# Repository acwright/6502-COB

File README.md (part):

6502-COB
========

An **AC6502** retro-style 8-bit computer based on the **65C02** microprocessor.

> 📖 **Guide:** [AC6502 Documentation](https://acwright.github.io/6502-DOCS/) — the user's and programmer's guide for the whole family.
> See [COB's page in the family appendix](https://acwright.github.io/6502-DOCS/family/cob).

---

**Building one? Every part you need, with supplier numbers and known issues, is in [BOM.md](BOM.md).**

## Table of Contents

- [Overview](#overview)
- [Architecture](#architecture)
- [Systems](#systems)
- [Software](#software)
- [Hardware](#hardware)
  - [Backplanes](#backplanes)
  - [Cards](#cards)
  - [Helpers](#helpers)
  - [Adapters](#adapters)
- [Which revision to make](#which-revision-to-make)
- [Works with the stock BIOS](#works-with-the-stock-bios)
- [Firmware](#firmware)
  - [KEH Controller](#keh-controller)
  - [PS2 Keyboard Controller](#ps2-keyboard-controller)
  - [SCP Controller](#scp-controller)
- [CAD](#cad)
- [Production](#production)
- [Schematics](#schematics)
- [Shared lines](#shared-lines)
- [Extra pins: `EXP0`–`EXP3` and `HRDB`](#extra-pins-exp0exp3-and-hrdb)
- [Jumpers](#jumpers)
- [Off-board headers](#off-board-headers)
- [Checking the schematics](#checking-the-schematics)
- [Libraries](#libraries)
- [Bill of Materials](#bill-of-materials)
- [Purchase](#purchase)
- [License](#license)

---

## Overview

The AC6502 ecosystem is a family of open-source, 65C02-based computers sharing a common architecture, memory map, and [BIOS](https://github.com/acwright/6502-BIOS). Each computer in the family is purpose-built for a different use case but runs the same software and firmware.

The **COB** (Computer on a Backplane) is a full-featured modular desktop computer. It features a real 65C02 CPU, a backplane architecture with expandable card slots, up to 544KB RAM, composite or VGA video output, CompactFlash or SD storage, a real-time clock, and support for PS/2 keyboards, matrix keyboards, and Atari 2600-compatible joysticks.

## Architecture

All AC6502 computers share:

- **CPU**: 65C02 (or accurate emulation)
- **Memory**: 32KB RAM + 32KB ROM, with optional banked RAM expansion
- **Memory Map**: Standardized across the ecosystem — zero page, stack, I/O space ($8000–$9FFF), system ROM, and interrupt vectors at $FFFA–$FFFF
- **Bus**: 16-bit address bus, 8-bit bidirectional data bus, standard 65C02 control signals (RW, PHI2, RESET, IRQ, NMI, RDY, SYNC)
- **BIOS**: A common [BIOS](https://github.com/acwright/6502-BIOS) provides the kernel, monitor, and BASIC interpreter across all systems

## Systems

| Project | Description |
|---------|-------------|
| [6502-ACE](https://github.com/acwright/6502-ACE) | All-in-one Computer Experience — A single board computer |
| [6502-COB](https://github.com/acwright/6502-COB) | Computer On a Backplane — Modular desktop computer with expandable card slots (YOU ARE HERE) |
| [6502-DEV](https://github.com/acwright/6502-DEV) | Development Environment Vehicle — Emulation-based dev system |
| [6502-KIM](https://github.com/acwright/6502-KIM) | Keypad Input Monitor - KIM-1 inspired minimal computer |
| [6502-VCS](https://github.com/acwright/6502-VCS) | Video Computer System — Cartridge-based retro gaming console |

## Software

| Project | Description |
|---------|-------------|
| [6502-BIOS](https://github.com/acwright/6502-BIOS) | The shared BIOS (kernel, monitor, BASIC) for all AC6502 computers |
| [6502-EMULATOR](https://github.com/acwright/6502-EMULATOR) | Emulator for the whole family — desktop app, browser build, and a command line for scripted runs |
| [6502-PRG](https://github.com/acwright/6502-PRG) | Template project for writing assembly language programs |
| [6502-CRT](https://github.com/acwright/6502-CRT) | Template project for writing assembly language cartridges |
| [6502-ASM](https://github.com/acwright/6502-ASM) | Assembly language example programs and demos |
| [6502-BAS](https://github.com/acwright/6502-BAS) | BASIC program listings |
| [6502-WOZMON](https://github.com/acwright/6502-WOZMON) | Wozmon as a standalone ROM |
| [6502-NOP](https://github.com/acwright/6502-NOP) | An all-NOP ROM, for probing a board during bring-up |
| [6502-DOCS](https://github.com/acwright/6502-DOCS) | The documentation site — the guide, the printable reference cards, branding and label artwork |
| [cffs](https://github.com/acwright/cffs) | Builds CompactFlash disk images for the BIOS filesystem |
| [bastok](https://github.com/acwright/bastok) | Tokenizes BASIC listings into `.prg` images, and back |
| [bin2woz](https://github.com/acwright/bin2woz) | Converts a binary into a Wozmon serial upload |

## Hardware

This repository contains KiCad 7.0+ PCB designs for the backplanes, cards, and helpers that make up the COB system.

### Backplanes

**`Hardware/Backplane/`** — Passive backplane providing 5 card slots with full bus interconnect across all slots.

**`Hardware/Backplane Pro/`** — Enhanced backplane with integrated clock generation, reset circuitry, and power distribution plus 5 card slots. Rev 1.1 moves to entirely through-hole components and adds an onboard power switch and DC barrel jack input. Today's Rev 1.1 also removes the `RESB` pull-up, which the boards made as Rev 1.1, on sale now, still have (see the build notes in BOM.md). Use a centre-positive 5 V supply: nothing on the board protects it from a reversed one. Every revision's oscillator can is 1 MHz, and serial is tested at 1 MHz. A faster can is at the builder's risk, because the serial cards haven't been tested with one.

**`Hardware/Backplane Helper/`** — Adds additional card slots to expand the total backplane configuration up to 12 slots.

### Cards

**`Hardware/Clock Card/`** — The Backplane Pro's clock, reset and power on a card, so a COB can be built on the passive Backplane: a 1 MHz DIP-14 can oscillator to `PHI2` through a clock-enable header (so the Clock Helper's single-step and halt still work), the 555 power-on and push-button reset pulling `RESB` low through an NPN, and a 5 V barrel jack straight to `VCC`, for a centre-positive supply only (a Rev 1.0 takes a wire link in place of D2; see the build notes in BOM.md). Serial is tested at 1 MHz, so a faster oscillator can is at the builder's risk, as on the Backplane Pro.

**`Hardware/CPU Card/`** — Hosts the 65C02 CPU in a card form factor for backplane-based COB systems. Its `EXP` header, J3, can jumper `EXP0` to VPB and `EXP1` to MLB. Leave those two positions open in a build that takes cartridges, because a cartridge grounds `EXP0` and `EXP1` (see [Extra pins](#extra-pins-exp0exp3-and-hrdb)).

**`Hardware/CPU Card Pro/`** — Hosts a 65816 16-bit CPU (backward-compatible with 65C02). *(Untested)* Its title block credits bahamutkotd, who contributed. Its `EXP` header, J3, can jumper `EXP0` to VPB and `EXP1` to MLB; as on the CPU Card, leave those positions open in a build that takes cartridges. J2, `BANK ADDR`, carries the 65816's bank byte (address bits A16–A23), which U4 latches while `PHI2` is low and holds through the rest of the cycle. It is how a 65816 on this card reaches past 64 KB, for a breadboard or a card of your own. Nothing in the family uses it yet, and it is unproven until the card is built. The RAM Card Rev 1.0's J4 has the same pinout; see its build notes before joining the two.

**`Hardware/Memory Card/`** — Provides 32KB SRAM and 32KB EEPROM with address decoding logic for COB systems using the CPU Card. J2 (or the solder jumpers JP1 and JP2) joins the bus's `EXP1` and `EXP0` to the ROM's `HRDB`: fit both in a COB that takes cartridges. See [Extra pins](#extra-pins-exp0exp3-and-hrdb).

**`Hardware/RAM Card/`** — 512KB banked RAM expansion organized as two 256KB banks with 256 × 1KB windows each. Rev 1.1 has the ACE Board's circuit, with a bank latch for each window; Rev 1.0 has one latch for both. Rev 1.0's J4, `BANK ADDR`, carries the bank latch's outputs: an untested experiment that nothing in the family uses, which the build notes in [BOM.md](BOM.md#ram-card) explain.

**`Hardware/RTC Card/`** — Real-time clock via Dallas DS1511Y with battery backup and 256 bytes of battery-backed SRAM. Any revision also takes the [RTC Adapter](#adapters), a cheaper DS1501 on a plug, and Rev 1.1 takes a bare DS1501, the same chip without the module's crystal and cell, with the crystal on the card; [BOM.md's build notes](BOM.md#build-notes) say what each needs.

**`Hardware/GPIO Card/`** — General-purpose I/O via 65C22 VIA supporting keyboards, joysticks, timers, and custom devices.

**`Hardware/Serial Card/`** — RS-232 serial communication via R6551AP ACIA and MAX232 level shifter.
Female DB-9 wired as **DCE**, so a straight-through cable reaches a PC. `DCD` and `DSR` are tied to
ground; `DTR` is not connected. The `CTS EN` jumper (J4) picks whether the ACIA's `CTS` comes from
ground or from the cable — **ground is the default**, which leaves the transmitter always free to
send. Serial is tested at 1 MHz, the speed of the oscillator can on the Backplane Pro and the Clock
Card. A faster can is at the builder's risk.

**`Hardware/Serial Card Pro/`** — Enhanced serial card with full modem control signals (DTR, DCD, DSR).
Male DB-9 wired as **DTE**, like a PC, so reaching a laptop needs a **null-modem** cable — unlike the
plain Serial Card. `CTS`, `DSR` and `DTR` always reach the cable; the `DCD EN` jumper picks ground or
the cable for `DCD` — **ground is the default**. Serial is tested at 1 MHz, the speed of the
oscillator can on the Backplane Pro and the Clock Card. A faster can is at the builder's risk.

**The handshake lines are not decoration.** On a real R6551, measured on a KIM in 2026: `CTS` high
stops the transmitter dead, and `DCD` high stops the receiver and the arriving byte is lost. A card
jumpered to take either from the cable, plugged into something that does not assert them, looks like
a dead board — no banner, no echo — until the line comes back. Ground is the default for exactly
that reason.

**`Hardware/VGA Card/`** — VGA 640×480 video output via Raspberry Pi Pico running [Pico9918](https://github.com/visrealm/pico9918) with TMS9918A-compatible graphics modes.

**`Hardware/Video Card/`** — Composite video output via TMS9918A Video Display Processor with 16KB video RAM.

**`Hardware/Sound Card/`** — 3-voice SID audio output via ARMSID module with RCA line-level output.

**`Hardware/Storage Card/`** — CompactFlash storage interface supporting up to 128GB via IDE-compatible protocol.

**`Hardware/Storage Card Pro/`** — SD card storage that the stock BIOS takes for the Storage Card's CompactFlash card, with no BIOS change, and a 16 MB built-in drive that answers when no card is in. A Raspberry Pi Pico 2 module does the work, running the [SCP Controller](#scp-controller). *(Untested: Rev 1.1 is drawn and routed, not yet made.)*

**`Hardware/LCD Card/`** — 16×2 character LCD display via 65C22 VIA in 4-bit or 8-bit mode.

**`Hardware/Blinkenlights Card/`** — Visual bus monitoring with LEDs showing address bus (16), data bus (8), and control signals (8) in real time.

**`Hardware/Prototype Card/`** — Blank prototyping area with integrated breadboard and full bus access headers.

### Helpers

**`Hardware/Keyboard Encoder Helper/`** — ATmega1284-based dual keyboard encoder supporting PS/2 keyboard and 8×8 matrix keyboard simultaneously via 65C22 VIA.

**`Hardware/PS2 Helper/`** — ATmega328p-based PS/2 keyboard bridge that drives an MT8808 analog crosspoint switch to emulate a matrix keyboard. Its output is a raw 8×8 matrix and feeds the matrix inputs of a Keyboard Encoder Helper, which is what talks to the 65C22 VIA — not the VIA directly.

**`Hardware/Keyboard Helper/`** — 64-key matrix keyboard with Atari 2600-compatible joystick support.

**`Hardware/GPIO Helper/`** — 8 buttons and 8 LEDs for testing and debugging GPIO Card connections.

**`Hardware/GPIO Breadboard Helper/`** — Breadboard interface adapter for the GPIO Card.

**`Hardware/Joystick Helper/`** — Atari 2600-style dual joystick connector and interface board.

**`Hardware/Clock Helper/`** — Manual clock control providing single-step, free-run, and halt modes for debugging real CPU systems.

**`Hardware/DB25 Helper/`** — GPIO to DB25 connector adapter for external device interfacing.

**`Hardware/Breadboard Helper/`** — Exposes the full AC6502 bus to a breadboard for prototyping and experimentation.

**`Hardware/Mega Helper/`** — Arduino Mega 2560 interface adapter for the AC6502 bus. Arduino pins D6 and D5 are wired to `EXP1` and `EXP0`: with a cartridge on the bus, firmware must leave them as inputs, because the cartridge grounds them (see [Extra pins](#extra-pins-exp0exp3-and-hrdb)).

**LCD Board** — moved to [6502-DEV](https://github.com/acwright/6502-DEV) as the DEV LCD Board on 2026-11-14: it is a DEV board.

**`Hardware/VERA Helper/`** — VERA FPGA video module adapter for the AC6502 bus.

### Adapters

**`Hardware/RTC Adapter/`** — A DS1501 real-time clock and its 32.768 kHz crystal on a DIP-28 plug, in place of the DS1511Y. The DS1511Y is a DS1501 with its crystal and a lithium cell in one module, and the family's most expensive chip: $41.36 at Digi-Key, against $23.19 for the adapter's DS1501YZN+ (2026-11-19). The adapter plugs into the DS1511Y's socket on any RTC Card or [ACE Board](https://github.com/acwright/6502-ACE#the-rtc), Rev 1.0 included, and fits inside the module's outline. The BIOS runs it as it runs the DS1511Y: the registers, the 256 bytes of NVRAM and the pinout are the same. The plug's pins 2, 3, 21 and 25 connect to nothing, so the adapter's crystal is never in parallel with a 1.1 board's own. *(Untested)*

Which RTC each board takes:

| Board | Rev | DS1511Y | RTC Adapter | DS1501 (DIP) |
|---|---|---|---|---|
| RTC Card | 1.0 | Yes, the part it was made and tested with | Yes, untested | No: it has no crystal |
| RTC Card | 1.1 | Yes | Yes, untested | Yes, untested |
| ACE Board | 1.0 | Yes, the part it was made and tested with | Yes, untested | No: it has no crystal |
| ACE Board | 1.1 | Yes | Yes, untested | Yes, untested |

With the RTC Adapter or a DS1501:
- **Keep the CR2032 fitted.** It is the DS1501's only backup, so taking it out loses the time and the NVRAM. A DS1511Y has its own cell as well.
- **Use BIOS 1.8 or 2.2.0 or later.** A new DS1501 may start with its Crystal Select bit set, and then it runs slow on the 6 pF crystal; the BIOS clears the bit at every boot from those releases on ([6502-BIOS #4](https://github.com/acwright/6502-BIOS/issues/4)).
- **The DS1501YN+, the DIP chip, is not for new designs** (NRND). The adapter's DS1501YZN+, in SOIC, is active.

[BOM.md's build notes](BOM.md#build-notes) say how to build the adapter.

<!-- Which revision to make: generated by Tools/revision-audit/register.py from Tools/data/orders.json. Edit that file, not this section. -->
## Which revision to make

**Make the newest revision of a board, and check its label first.** The table below gives each board's newest revision. A newer revision fixes what was found on the older ones. Every revision, old and new, is in [REVISIONS.md](REVISIONS.md), with what changed in each.

Each revision carries one of three labels:

- **Tested:** This revision was built and tested.
- **Proven design:** Not built at this revision, but its circuit is proven. Either it is a tested revision's circuit, or each change copies a circuit built and tested on another board or on the bench, or is a textbook circuit that leaves everything the tested revision does as it was. Any other change is silkscreen text, part values, mounting holes, outline clean-up, parts moved a fraction of a millimetre onto their grid, capacitor pitch, socket outlines, a footprint swap with the same holes, a solder jumper's default, the solder mask or paste at a card edge, or tracks rerouted or pours refilled with DRC and the netlist check passing. A builder can treat it as tested.
- **Untested:** The circuit, the power path or the layout changed in a way that only a built board proves, or the board has never been built at all.

[BOM.md](BOM.md) has the parts for every revision, and its known issues.

| Board | Newest revision | Label | Why |
|---|---|---|---|
| Backplane | 1.1 | **Proven design** | JLCPCB's marker removed and the logo moved; silkscreen only. |
| Backplane Helper | 1.1 | **Proven design** | JLCPCB's marker removed and the logo moved; silkscreen only. |
| Backplane Pro | 1.1 | **Proven design** | The tested boards made as Rev 1.1, with R5, a second pull-up on `RESB` beside the CPU Card's, left off. Nothing else changed. |
| Blinkenlights Card | 1.1 | **Untested** | Decoupling capacitors added, the RESB, IRQB and NMIB LEDs driven through inverters, every inverter a 74HC3G04, tracks rerouted, and the bare card edge. |
| Breadboard Helper | 1.1 | **Proven design** | J1 takes the box header's footprint, with the same holes, and the outline grows to hold it. |
| CPU Card | 1.1 | **Proven design** | 10k pull-ups, some tracks rerouted, silkscreen, the bare card edge. |
| CPU Card Pro | 1.1 | **Untested** | Never made. |
| Clock Card | 1.1 | **Proven design** | The bare card edge only. |
| Clock Helper | 1.1 | **Proven design** | Mounting holes moved to the standard, silkscreen. |
| DB25 Helper | 1.1 | **Proven design** | Mounting holes moved to the standard, silkscreen. |
| GPIO Breadboard Helper | 1.1 | **Proven design** | Outline clean-up. |
| GPIO Card | 1.1 | **Proven design** | The bare card edge only. |
| GPIO Helper | 1.1 | **Proven design** | Mounting holes moved to the standard, silkscreen. |
| Joystick Helper | 1.1 | **Proven design** | Mounting holes moved to the standard, silkscreen. |
| Keyboard Encoder Helper | 1.1 | **Proven design** | Mounting holes, silkscreen, and 10k pull-ups on the PS/2 lines, a textbook circuit not yet tried on these lines. |
| Keyboard Helper | 1.1 | **Proven design** | JLCPCB's marker removed and the logo moved; silkscreen only. |
| LCD Card | 1.1 | **Proven design** | The bare card edge only. |
| Mega Helper | 1.1 | **Proven design** | JLCPCB's marker removed, J1's reference resized and the logo moved; silkscreen only. |
| Memory Card | 1.1 | **Proven design** | The bare card edge only. |
| PS2 Helper | 1.1 | **Proven design** | Resistors moved and tracks rerouted, mounting holes, silkscreen, and 10k pull-ups on the PS/2 lines, a textbook circuit not yet tried on these lines. |
| Prototype Card | 1.1 | **Proven design** | The bare card edge only. |
| RAM Card | 1.1 | **Proven design** | The ACE's banked-RAM circuit, tested as the ACE RAM Patch 1.1: a bank latch for each window and a diode chip select (BAT54s in the BAT85s' place). The window decode is Rev 1.0's, and the `LATCH EN` and `BANK ADDR` headers are gone. Tracks rerouted, with the decode check passing in every window. |
| RTC Adapter | 1.1 | **Untested** | A new board: a DS1501 in SOIC and its crystal on a DIP-28 plug, for the DS1511Y's socket on any RTC Card or ACE Board. Not yet made. |
| RTC Card | 1.1 | **Proven design** | The bare card edge, and JP2 and JP3 removed, wired as Rev 1.0 ships them. The DS1501 option at U1, with its crystal `Y1`, is untested. |
| Serial Card | 1.1 | **Proven design** | Silkscreen text and the bare card edge. |
| Serial Card Pro | 1.1 | **Proven design** | The DB-9 moved to KiCad's standard footprint (the same connector), tracks rerouted, silkscreen, the bare card edge. |
| Sound Card | 1.1 | **Proven design** | Silkscreen text, the bare card edge, and a second RCA jack on the same signal, as on the ACE. |
| Storage Card | 1.1 | **Proven design** | The bare card edge only. |
| Storage Card Pro | 1.1 | **Untested** | Redesigned: an SD card the stock BIOS takes for CompactFlash, with a built-in drive. Not yet made. |
| VERA Helper | 1.1 | **Proven design** | Mounting holes, capacitor pitch, JP2 ships open, JP1 and JP3 removed and wired as Rev 1.0 ships them. |
| VGA Card | 1.1 | **Proven design** | `A1` wired to the pico9918's `MODE1`, as on the tested ACE; JP1 open, so `/INT` passes only through D1, as the ACE's video card runs; `PHI2` wired to U3 as Rev 1.0 ships, with JP2 and JP3 gone. The pico9918 is turned around with its tracks rerouted, the notch and holes for its VGA adapter moved, and the card edge bare. |
| Video Card | 1.1 | **Proven design** | JP7, a solder jumper, ships bridged (fine with a real TMS9918A's open-drain `/INT`), JP1–JP6 removed and wired as Rev 1.0 ships them, sockets, silkscreen, the bare card edge. |
<!-- End of which revision to make -->

<!-- Stock BIOS: generated by Tools/bios/gen.py from Tools/data/bios.json. Edit that file, not this section. -->
## Works with the stock BIOS

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
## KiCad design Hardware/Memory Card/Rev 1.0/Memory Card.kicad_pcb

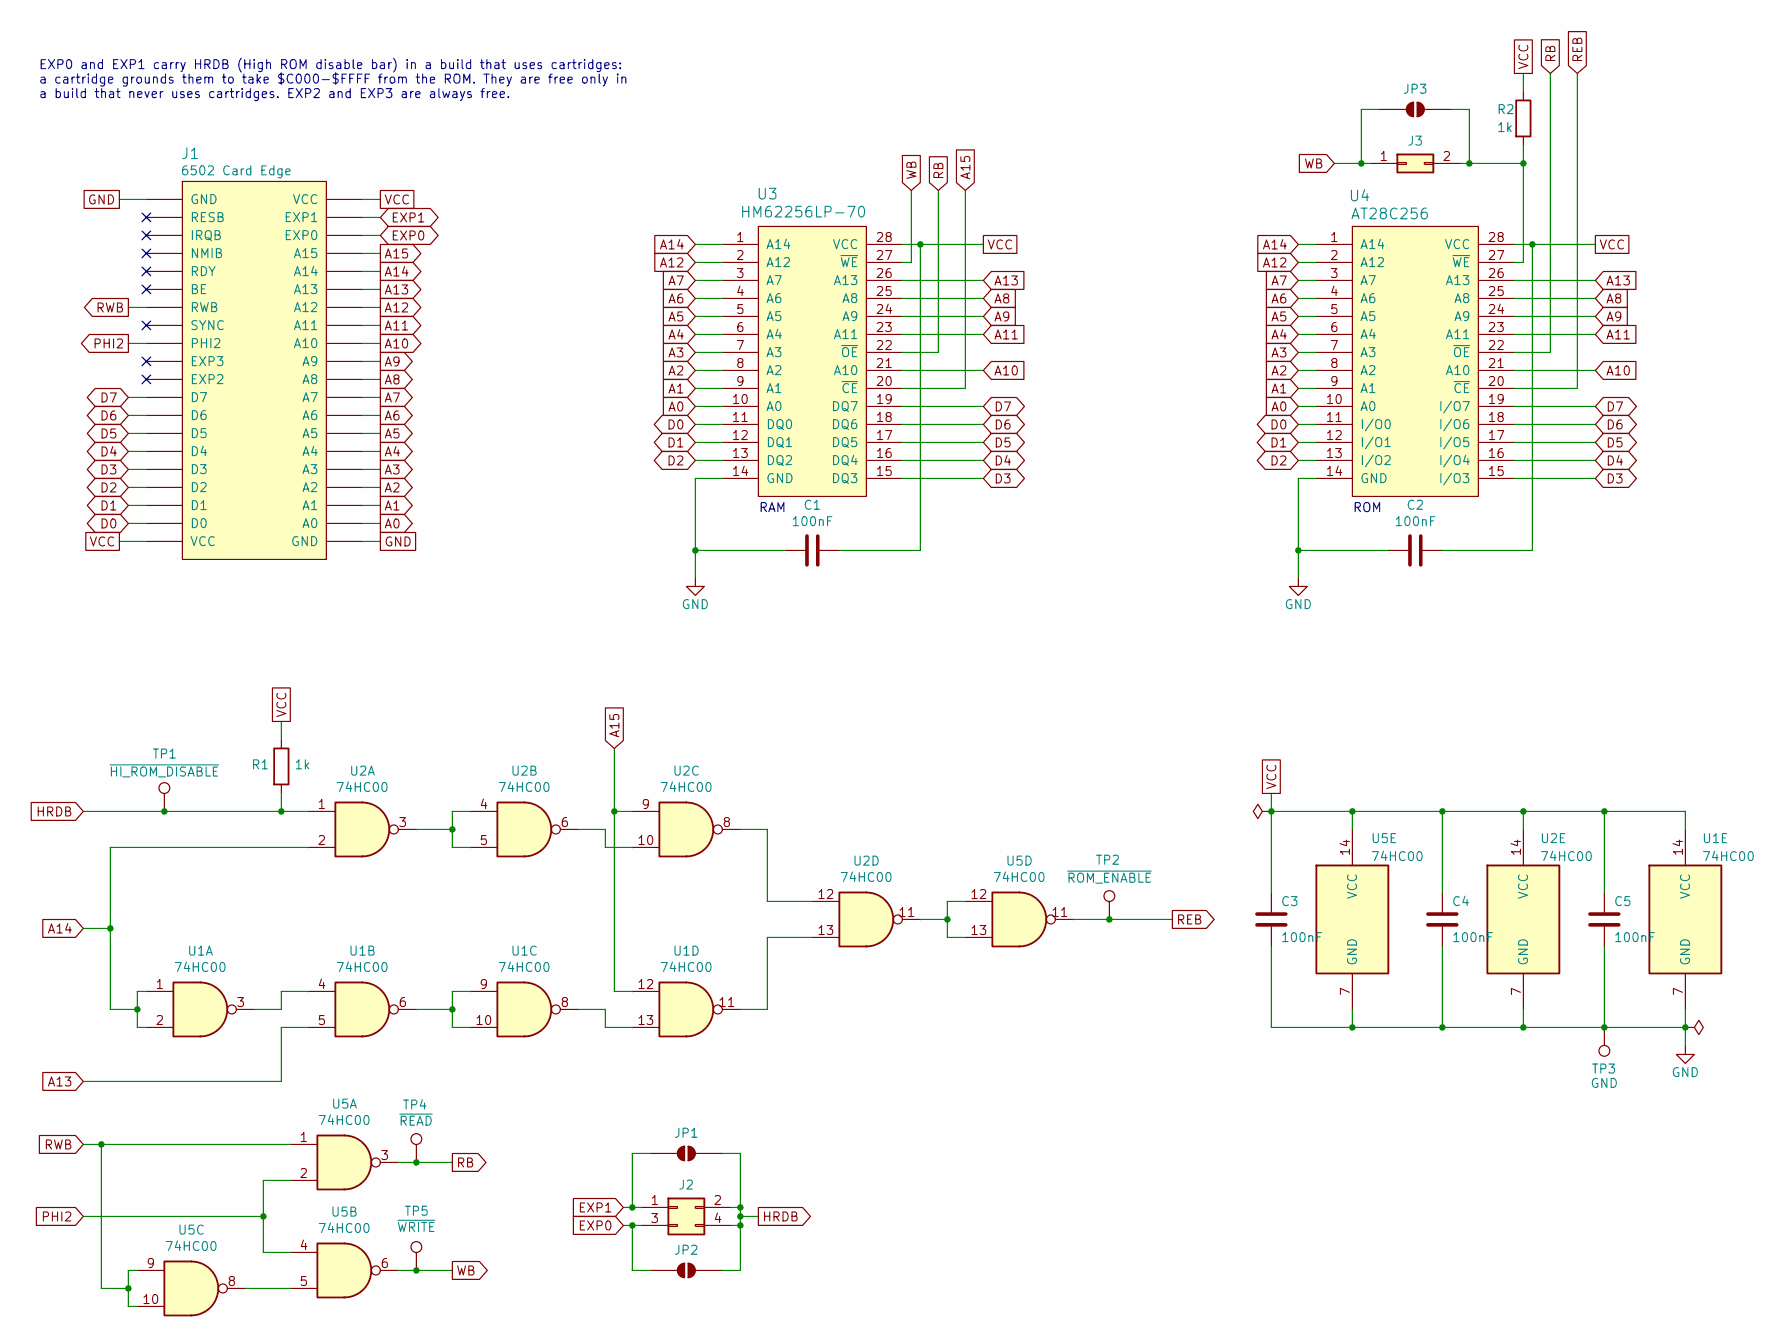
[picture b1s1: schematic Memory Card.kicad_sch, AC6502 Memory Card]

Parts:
C1, C2, C3, C4, C5: 100nF; C_0805_2012Metric; LCSC C49678
J1: 6502 Card Edge
J2: Conn_02x02_Odd_Even; PinHeader_2x02_P2.54mm_Vertical; Digikey S2011EC-40-ND
J3: Conn_02x01; PinHeader_1x02_P2.54mm_Vertical; Digikey S1011EC-40-ND
JP1, JP2, JP3: SolderJumper_2_Open; SolderJumper-2_P1.3mm_Open_RoundedPad1.0x1.5mm
R1, R2: 1k; R_0805_2012Metric; LCSC C17513
TP1: ~{HI_ROM_DISABLE}; TestPoint_Pad_1.0x1.0mm
TP2: ~{ROM_ENABLE}; TestPoint_Pad_1.0x1.0mm
TP3: GND; TestPoint_Pad_1.0x1.0mm
TP4: ~{READ}; TestPoint_Pad_1.0x1.0mm
TP5: ~{WRITE}; TestPoint_Pad_1.0x1.0mm
U1, U2, U5: 74HC00; SOIC-14_3.9x8.7mm_P1.27mm; LCSC C5586
U3: HM62256LP-70; DIP-28_W15.24mm_Socket_LongPads
U4: AT28C256; DIP-28_W15.24mm_Socket_LongPads; Digikey AT28C256-15PU-ND

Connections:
A0: J1.A0, U3.10 (A0), U4.10 (A0)
A1: J1.A1, U3.9 (A1), U4.9 (A1)
A2: J1.A2, U3.8 (A2), U4.8 (A2)
A3: J1.A3, U3.7 (A3), U4.7 (A3)
A4: J1.A4, U3.6 (A4), U4.6 (A4)
A5: J1.A5, U3.5 (A5), U4.5 (A5)
A6: J1.A6, U3.4 (A6), U4.4 (A6)
A7: J1.A7, U3.3 (A7), U4.3 (A7)
A8: J1.A8, U3.25 (A8), U4.25 (A8)
A9: J1.A9, U3.24 (A9), U4.24 (A9)
A10: J1.A10, U3.21 (A10), U4.21 (A10)
A11: J1.A11, U3.23 (A11), U4.23 (A11)
A12: J1.A12, U3.2 (A12), U4.2 (A12)
A13: J1.A13, U1.5, U3.26 (A13), U4.26 (A13)
A14: J1.A14, U1.1, U1.2, U2.2, U3.1 (A14), U4.1 (A14)
A15: J1.A15, U1.12, U2.9, U3.20 (~CE)
D0: J1.D0, U3.11 (DQ0), U4.11 (I/O0)
D1: J1.D1, U3.12 (DQ1), U4.12 (I/O1)
D2: J1.D2, U3.13 (DQ2), U4.13 (I/O2)
D3: J1.D3, U3.15 (DQ3), U4.15 (I/O3)
D4: J1.D4, U3.16 (DQ4), U4.16 (I/O4)
D5: J1.D5, U3.17 (DQ5), U4.17 (I/O5)
D6: J1.D6, U3.18 (DQ6), U4.18 (I/O6)
D7: J1.D7, U3.19 (DQ7), U4.19 (I/O7)
EXP0: J1.EXP0, J2.3, JP2.1 (A)
EXP1: J1.EXP1, J2.1, JP1.1 (A)
GND: C1.2, C2.2, C3.2, C4.2, C5.2, J1.GND, TP3.1, U1.7 (GND), U2.7 (GND), U3.14 (GND), U4.14 (GND), U5.7 (GND)
HRDB: J2.2, J2.4, JP1.2 (B), JP2.2 (B), R1.2, TP1.1, U2.1
unnamed: J3.2, JP3.2 (B), R2.2, U4.27 (~WE)
unnamed: U1.3, U1.4
unnamed: U1.6, U1.9, U1.10
unnamed: U1.11, U2.13
unnamed: U1.8, U1.13
unnamed: U2.3, U2.4, U2.5
unnamed: U2.6, U2.10
unnamed: U2.11, U5.12, U5.13
unnamed: U2.8, U2.12
unnamed: U5.5, U5.8
PHI2: J1.PHI2, U5.2, U5.4
RB: TP4.1, U3.22 (~OE), U4.22 (~OE), U5.3
REB: TP2.1, U4.20 (~CE), U5.11
RWB: J1.RWB, U5.1, U5.9, U5.10
VCC: C1.1, C2.1, C3.1, C4.1, C5.1, J1.VCC, R1.1, R2.1, U1.14 (VCC), U2.14 (VCC), U3.28 (VCC), U4.28 (VCC), U5.14 (VCC)
WB: J3.1, JP3.1 (A), TP5.1, U3.27 (~WE), U5.6

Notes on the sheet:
RAM
ROM
EXP0 and EXP1 carry HRDB (High ROM disable bar) in a build that uses cartridges: a cartridge grounds them to take $C000-$FFFF from the ROM. They are free only in a build that never uses cartridges. EXP2 and EXP3 are always free.

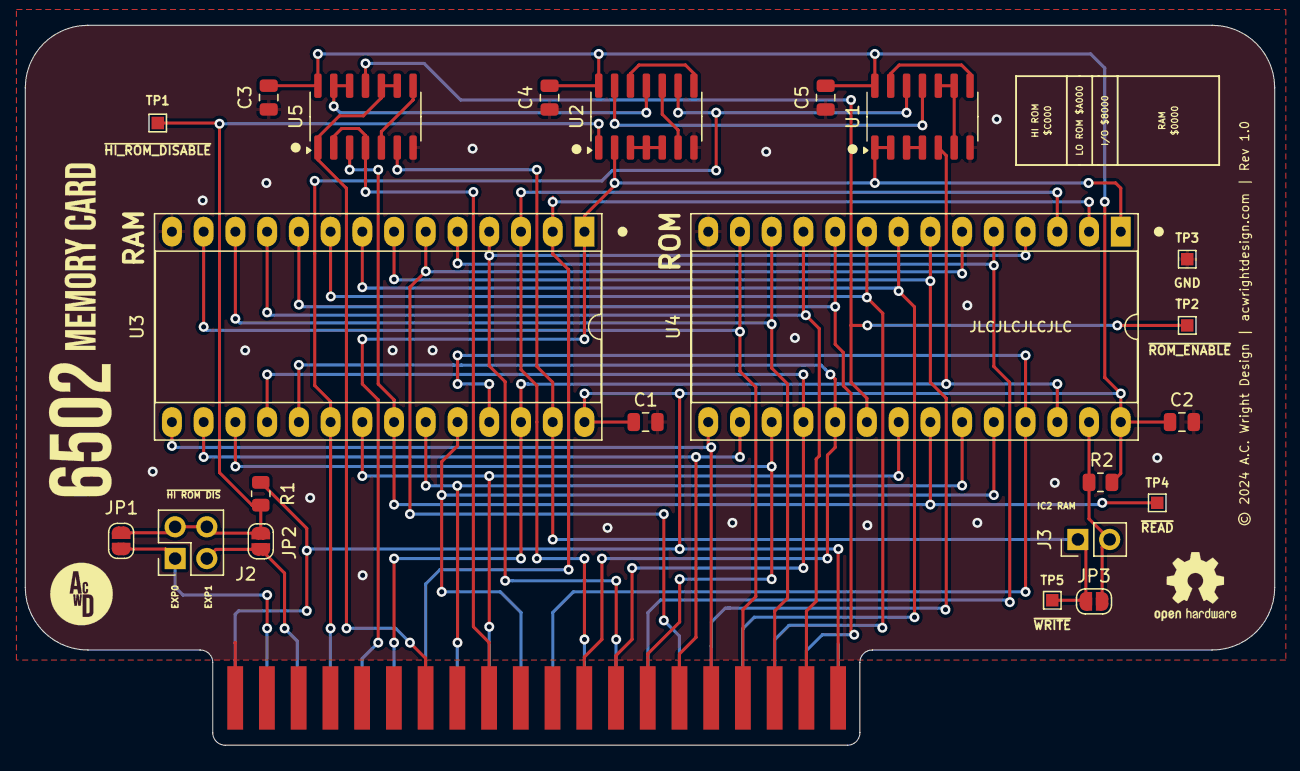
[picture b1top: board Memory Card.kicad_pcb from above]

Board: 2 copper layers, 100.0 x 57.6 mm, 23 parts (0 on the bottom side), 44 nets.

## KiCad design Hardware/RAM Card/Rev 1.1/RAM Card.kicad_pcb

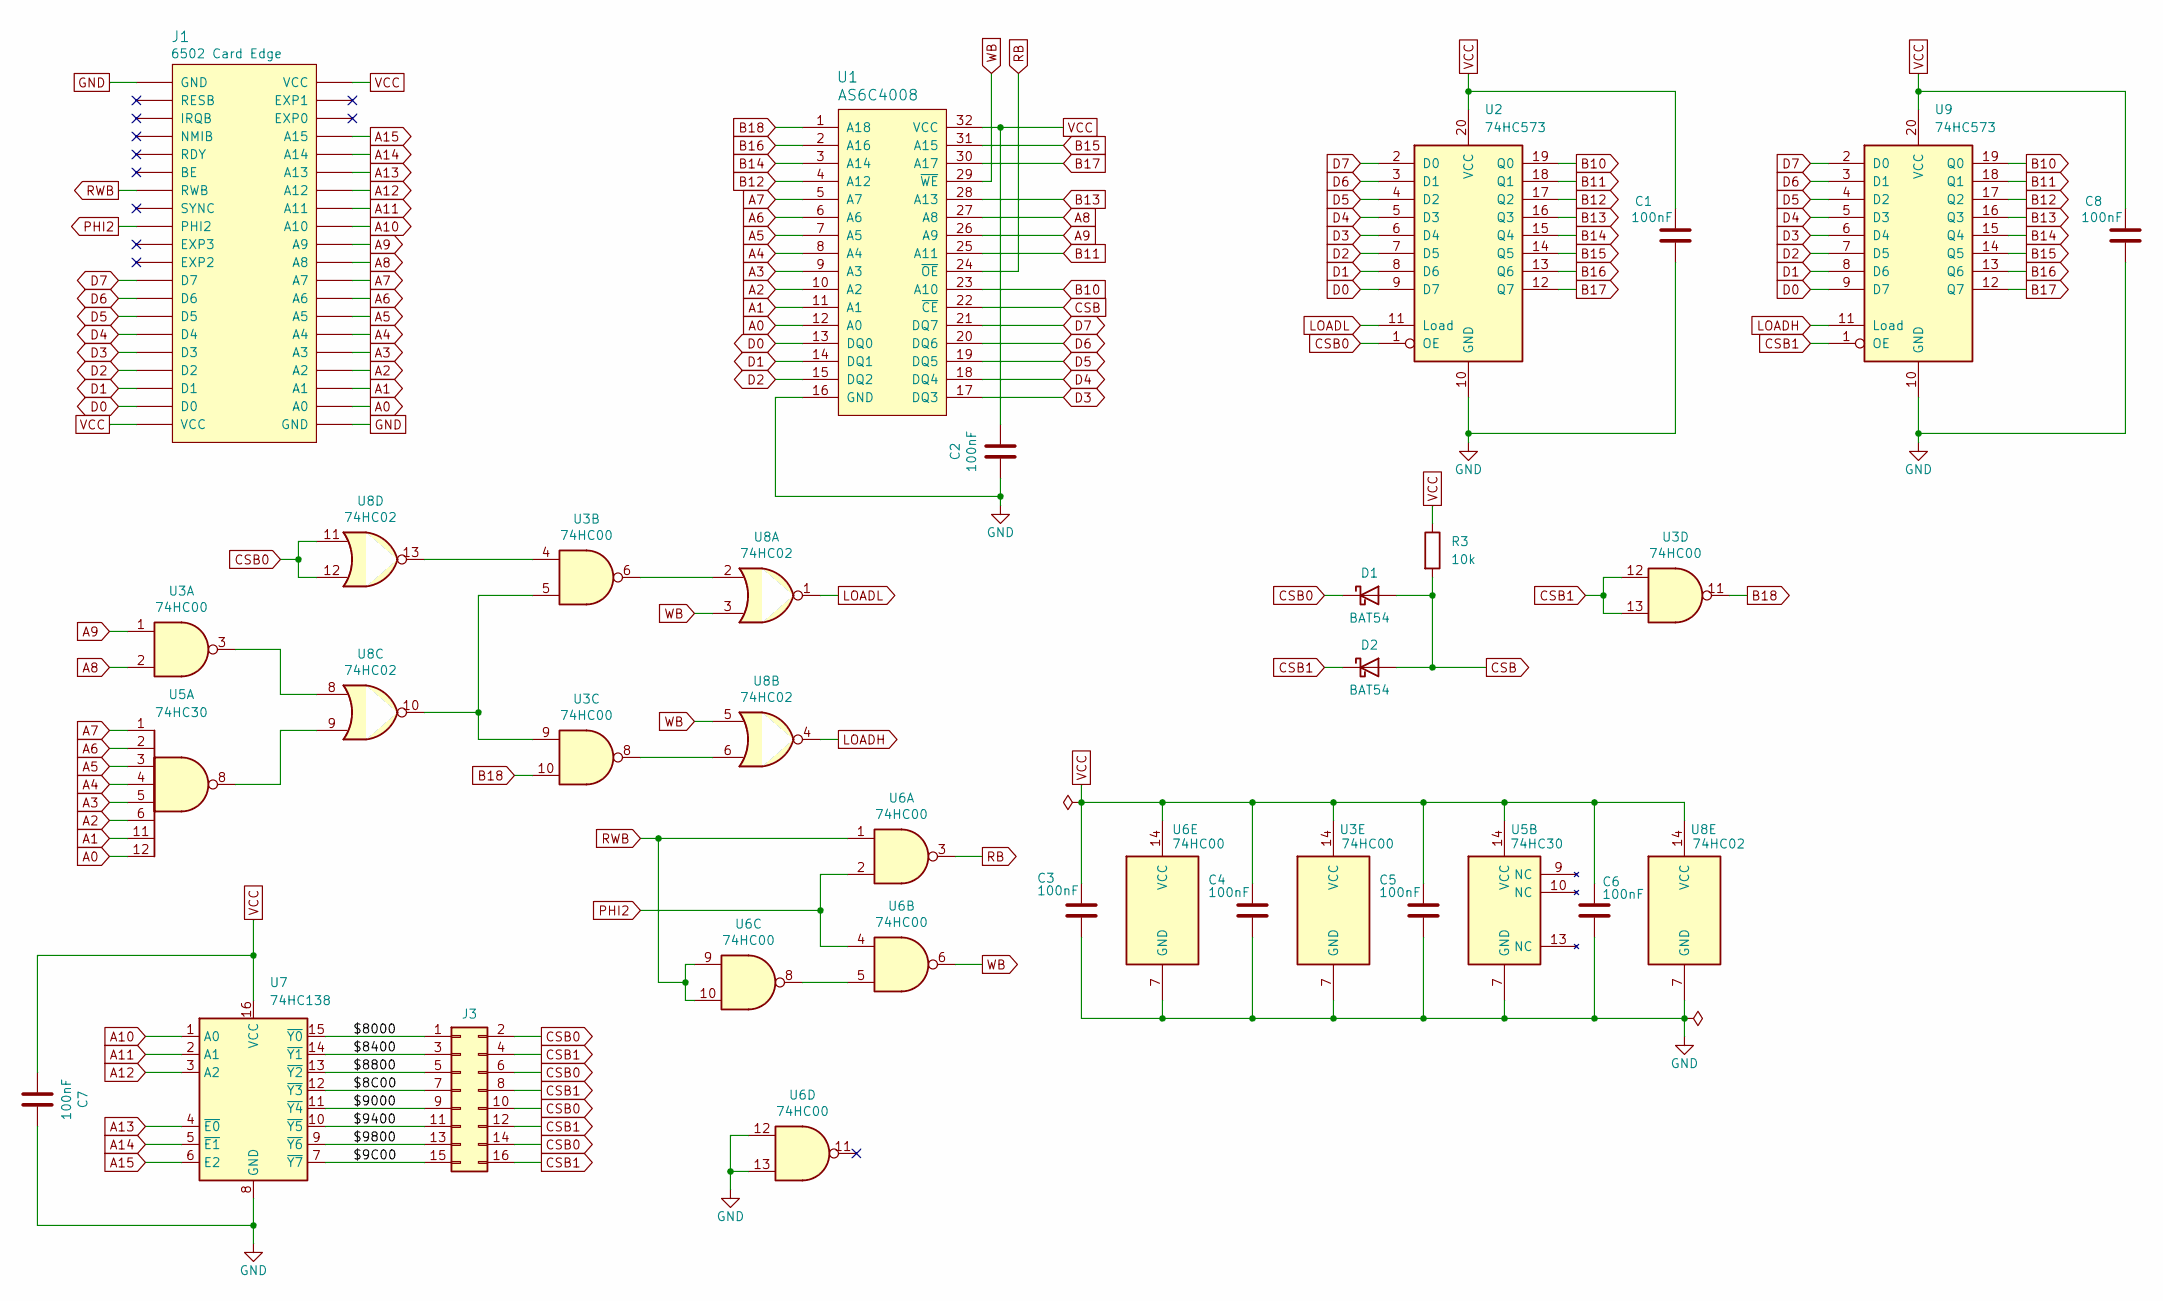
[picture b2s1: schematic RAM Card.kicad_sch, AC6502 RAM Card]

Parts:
C1, C2, C3, C4, C5, C6, C7, C8: 100nF; C_0805_2012Metric; LCSC C49678
D1, D2: BAT54; D_SOD-123; LCSC C152458
J1: 6502 Card Edge
J3: Conn_02x08_Odd_Even; PinHeader_2x08_P2.54mm_Vertical; Digikey S2011EC-40-ND
R3: 10k; R_0805_2012Metric; LCSC C17414
U1: AS6C4008; DIP-32_W15.24mm_Socket_LongPads; Digikey 1450-1027-ND
U2, U9: 74HC573; SOIC-20W_7.5x12.8mm_P1.27mm; LCSC C5608
U3, U6: 74HC00; SOIC-14_3.9x8.7mm_P1.27mm; LCSC C5586
U5: 74HC30; SOIC-14_3.9x8.7mm_P1.27mm; LCSC C19818870
U7: 74HC138; SOIC-16_3.9x9.9mm_P1.27mm; LCSC C5602
U8: 74HC02; SOIC-14_3.9x8.7mm_P1.27mm; LCSC C5588

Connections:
/$8C00: J3.7, U7.12 (~Y3)
/$9C00: J3.15, U7.7 (~Y7)
/$8000: J3.1, U7.15 (~Y0)
/$8400: J3.3, U7.14 (~Y1)
/$8800: J3.5, U7.13 (~Y2)
/$9000: J3.9, U7.11 (~Y4)
/$9400: J3.11, U7.10 (~Y5)
/$9800: J3.13, U7.9 (~Y6)
A0: J1.A0, U1.12 (A0), U5.12
A1: J1.A1, U1.11 (A1), U5.11
A2: J1.A2, U1.10 (A2), U5.6
A3: J1.A3, U1.9 (A3), U5.5
A4: J1.A4, U1.8 (A4), U5.4
A5: J1.A5, U1.7 (A5), U5.3
A6: J1.A6, U1.6 (A6), U5.2
A7: J1.A7, U1.5 (A7), U5.1
A8: J1.A8, U1.27 (A8), U3.2
A9: J1.A9, U1.26 (A9), U3.1
A10: J1.A10, U7.1 (A0)
A11: J1.A11, U7.2 (A1)
A12: J1.A12, U7.3 (A2)
A13: J1.A13, U7.4 (~E0)
A14: J1.A14, U7.5 (~E1)
A15: J1.A15, U7.6 (E2)
B10: U1.23 (A10), U2.19 (Q0), U9.19 (Q0)
B11: U1.25 (A11), U2.18 (Q1), U9.18 (Q1)
B12: U1.4 (A12), U2.17 (Q2), U9.17 (Q2)
B13: U1.28 (A13), U2.16 (Q3), U9.16 (Q3)
B14: U1.3 (A14), U2.15 (Q4), U9.15 (Q4)
B15: U1.31 (A15), U2.14 (Q5), U9.14 (Q5)
B16: U1.2 (A16), U2.13 (Q6), U9.13 (Q6)
B17: U1.30 (A17), U2.12 (Q7), U9.12 (Q7)
B18: U1.1 (A18), U3.10, U3.11
CSB: D1.2 (A), D2.2 (A), R3.2, U1.22 (~CE)
CSB0: D1.1 (K), J3.2, J3.6, J3.10, J3.14, U2.1 (OE), U8.11, U8.12
CSB1: D2.1 (K), J3.4, J3.8, J3.12, J3.16, U3.12, U3.13, U9.1 (OE)
D0: J1.D0, U1.13 (DQ0), U2.9 (D7), U9.9 (D7)
D1: J1.D1, U1.14 (DQ1), U2.8 (D6), U9.8 (D6)
D2: J1.D2, U1.15 (DQ2), U2.7 (D5), U9.7 (D5)
D3: J1.D3, U1.17 (DQ3), U2.6 (D4), U9.6 (D4)
D4: J1.D4, U1.18 (DQ4), U2.5 (D3), U9.5 (D3)
D5: J1.D5, U1.19 (DQ5), U2.4 (D2), U9.4 (D2)
D6: J1.D6, U1.20 (DQ6), U2.3 (D1), U9.3 (D1)
D7: J1.D7, U1.21 (DQ7), U2.2 (D0), U9.2 (D0)
GND: C1.2, C2.2, C3.2, C4.2, C5.2, C6.2, C7.2, C8.2, J1.GND, U1.16 (GND), U2.10 (GND), U3.7 (GND), U5.7 (GND), U6.7 (GND), U6.12, U6.13, U7.8 (GND), U8.7 (GND), U9.10 (GND)
LOADH: U8.4, U9.11 (Load)
LOADL: U2.11 (Load), U8.1
unnamed: U3.3, U8.8
unnamed: U3.4, U8.13
unnamed: U3.5, U3.9, U8.10
unnamed: U3.6, U8.2
unnamed: U3.8, U8.6
unnamed: U5.8, U8.9
unnamed: U6.5, U6.8
PHI2: J1.PHI2, U6.2, U6.4
RB: U1.24 (~OE), U6.3
RWB: J1.RWB, U6.1, U6.9, U6.10
VCC: C1.1, C2.1, C3.1, C4.1, C5.1, C6.1, C7.1, C8.1, J1.VCC, R3.1, U1.32 (VCC), U2.20 (VCC), U3.14 (VCC), U5.14 (VCC), U6.14 (VCC), U7.16 (VCC), U8.14 (VCC), U9.20 (VCC)
WB: U1.29 (~WE), U6.6, U8.3, U8.5

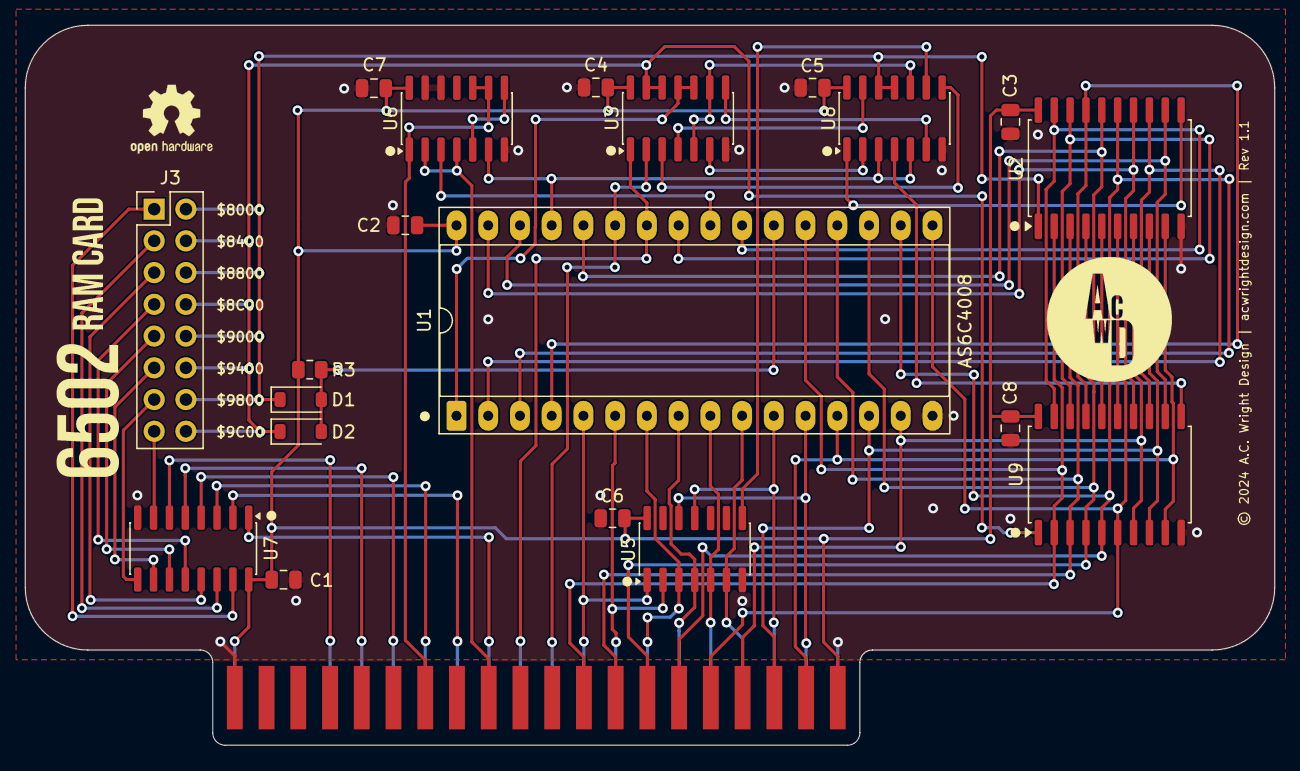
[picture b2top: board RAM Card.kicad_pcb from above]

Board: 2 copper layers, 100.0 x 57.6 mm, 21 parts (0 on the bottom side), 59 nets.

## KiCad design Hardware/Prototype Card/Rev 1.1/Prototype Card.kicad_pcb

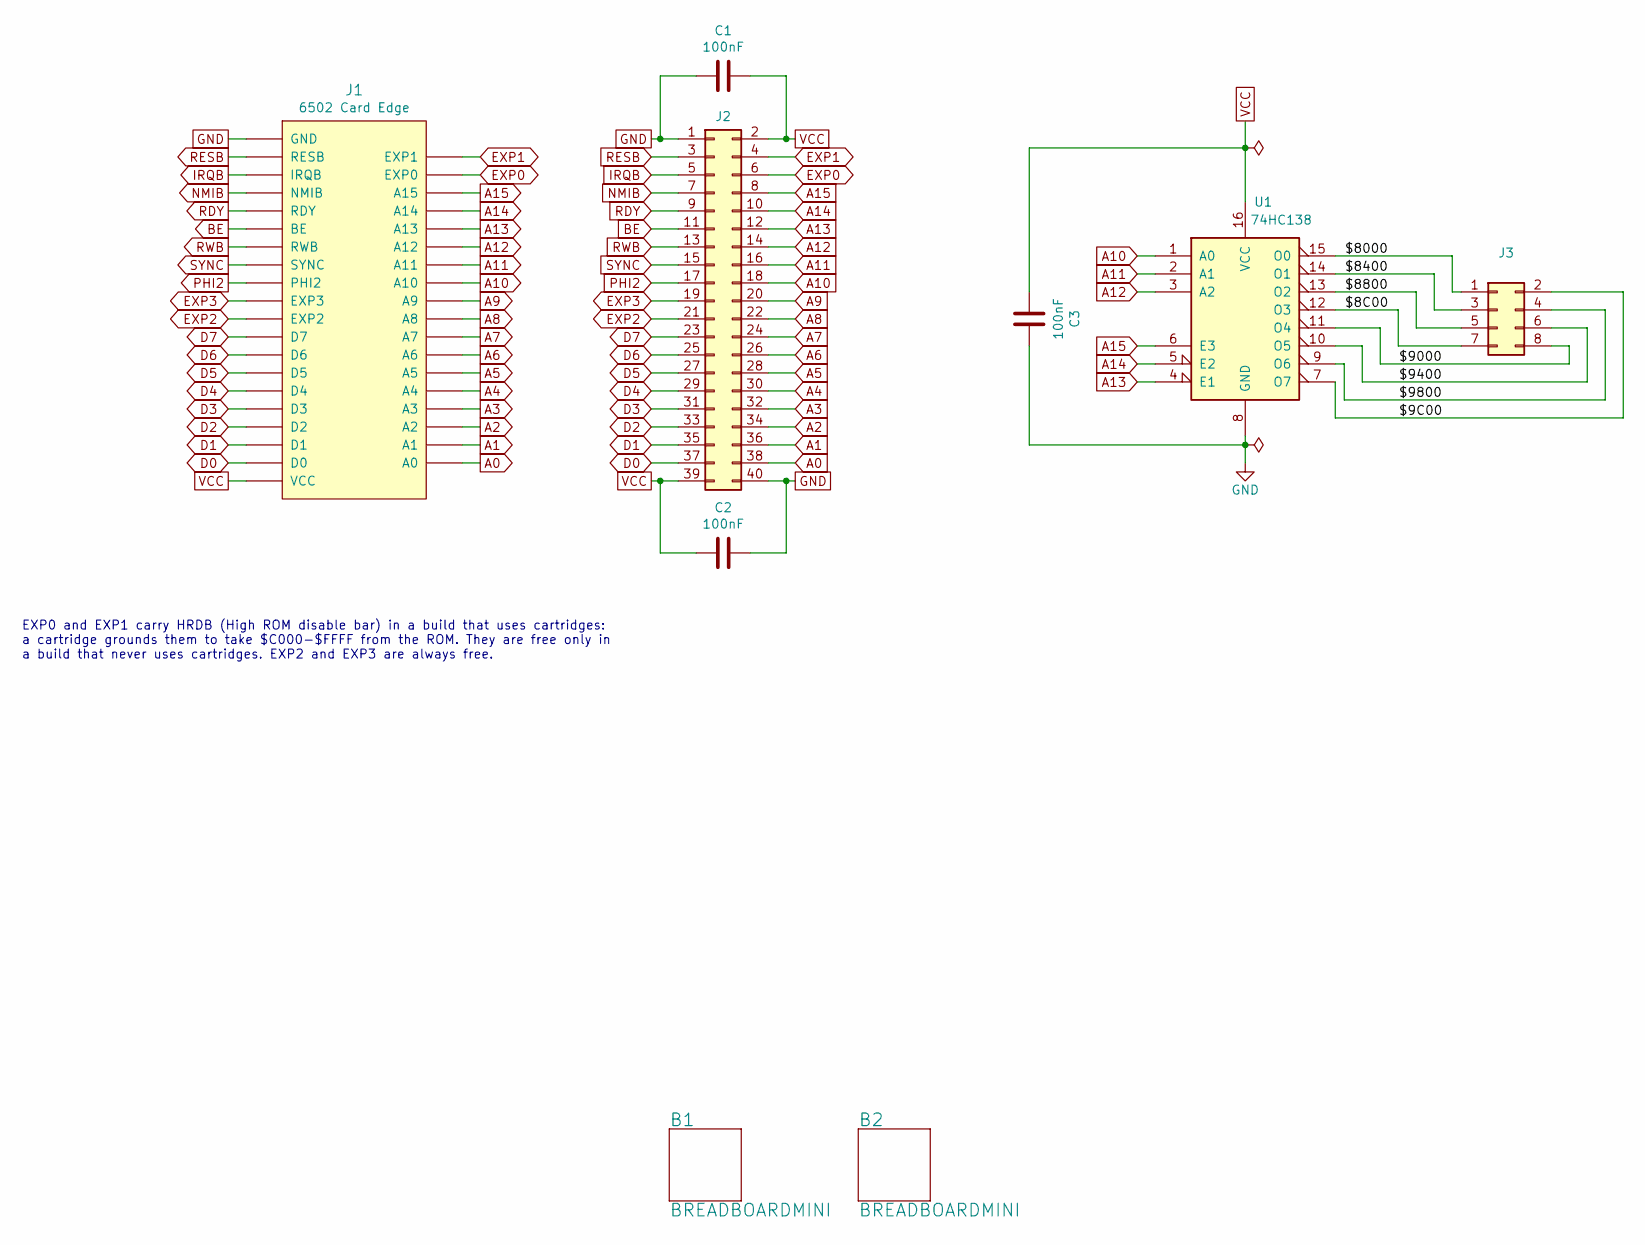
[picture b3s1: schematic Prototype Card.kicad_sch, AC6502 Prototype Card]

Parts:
B1, B2: BREADBOARDMINI; Breadboard Mini; Mouser 474-PRT-12047
C1, C2, C3: 100nF; C_0805_2012Metric; LCSC C49678
J1: 6502 Card Edge
J2: 6502 Bus; PinSocket_2x20_P2.54mm_Vertical; Digikey S7123-ND
J3: Conn_02x04_Odd_Even; PinHeader_2x04_P2.54mm_Vertical; Digikey S2011EC-40-ND
U1: 74HC138; SOIC-16_3.9x9.9mm_P1.27mm; LCSC C5602

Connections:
/$8C00: J3.7, U1.12 (O3)
/$9C00: J3.2, U1.7 (O7)
/$8000: J3.1, U1.15 (O0)
/$8400: J3.3, U1.14 (O1)
/$8800: J3.5, U1.13 (O2)
/$9000: J3.8, U1.11 (O4)
/$9400: J3.6, U1.10 (O5)
/$9800: J3.4, U1.9 (O6)
A0: J1.A0, J2.38
A1: J1.A1, J2.36
A2: J1.A2, J2.34
A3: J1.A3, J2.32
A4: J1.A4, J2.30
A5: J1.A5, J2.28
A6: J1.A6, J2.26
A7: J1.A7, J2.24
A8: J1.A8, J2.22
A9: J1.A9, J2.20
A10: J1.A10, J2.18, U1.1 (A0)
A11: J1.A11, J2.16, U1.2 (A1)
A12: J1.A12, J2.14, U1.3 (A2)
A13: J1.A13, J2.12, U1.4 (E1)
A14: J1.A14, J2.10, U1.5 (E2)
A15: J1.A15, J2.8, U1.6 (E3)
BE: J1.BE, J2.11
D0: J1.D0, J2.37
D1: J1.D1, J2.35
D2: J1.D2, J2.33
D3: J1.D3, J2.31
D4: J1.D4, J2.29
D5: J1.D5, J2.27
D6: J1.D6, J2.25
D7: J1.D7, J2.23
EXP0: J1.EXP0, J2.6
EXP1: J1.EXP1, J2.4
EXP2: J1.EXP2, J2.21
EXP3: J1.EXP3, J2.19
GND: C1.1, C2.2, C3.2, J1.GND, J2.1, J2.40, U1.8 (GND)
IRQB: J1.IRQB, J2.5
NMIB: J1.NMIB, J2.7
PHI2: J1.PHI2, J2.17
RDY: J1.RDY, J2.9
RESB: J1.RESB, J2.3
RWB: J1.RWB, J2.13
SYNC: J1.SYNC, J2.15
VCC: C1.2, C2.1, C3.1, J1.VCC, J2.2, J2.39, U1.16 (VCC)

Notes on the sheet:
EXP0 and EXP1 carry HRDB (High ROM disable bar) in a build that uses cartridges: a cartridge grounds them to take $C000-$FFFF from the ROM. They are free only in a build that never uses cartridges. EXP2 and EXP3 are always free.

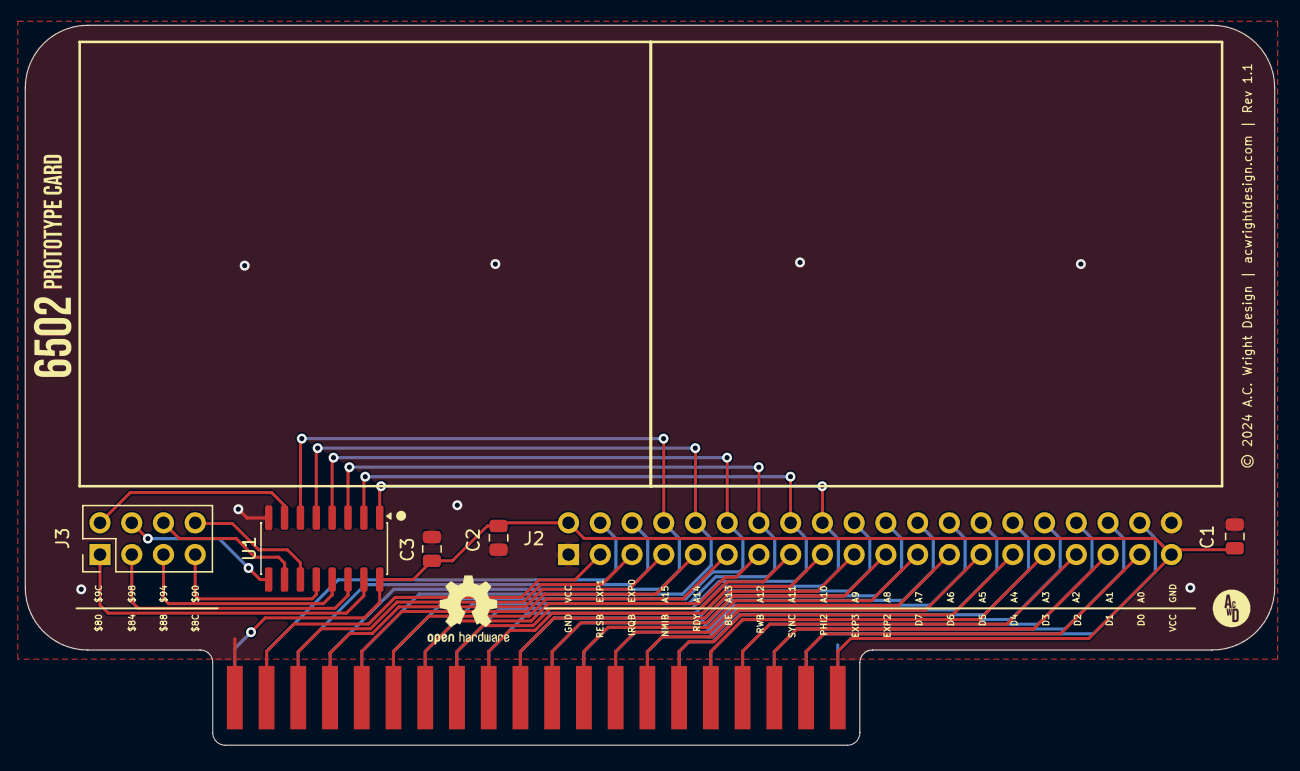
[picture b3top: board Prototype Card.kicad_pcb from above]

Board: 2 copper layers, 100.0 x 57.6 mm, 9 parts (1 on the bottom side), 46 nets.

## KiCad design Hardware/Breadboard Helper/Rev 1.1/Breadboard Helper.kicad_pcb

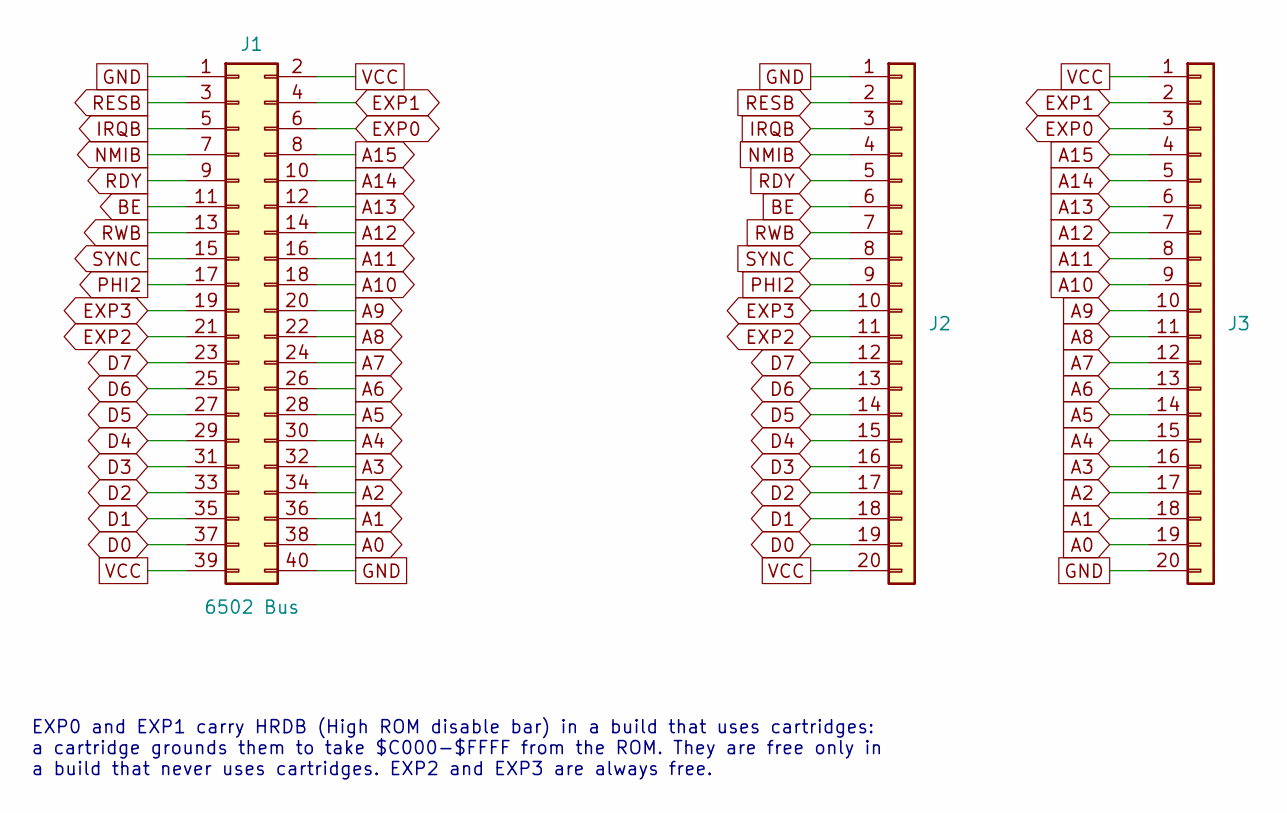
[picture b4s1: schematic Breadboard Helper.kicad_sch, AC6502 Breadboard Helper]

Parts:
J1: 6502 Bus; 6502 Bus Connector; Digikey 732-5401-ND
J2, J3: Conn_01x20; PinHeader_1x20_P2.54mm_Vertical; Digikey S1011EC-40-ND

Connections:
A0: J1.38, J3.19
A1: J1.36, J3.18
A2: J1.34, J3.17
A3: J1.32, J3.16
A4: J1.30, J3.15
A5: J1.28, J3.14
A6: J1.26, J3.13
A7: J1.24, J3.12
A8: J1.22, J3.11
A9: J1.20, J3.10
A10: J1.18, J3.9
A11: J1.16, J3.8
A12: J1.14, J3.7
A13: J1.12, J3.6
A14: J1.10, J3.5
A15: J1.8, J3.4
BE: J1.11, J2.6
D0: J1.37, J2.19
D1: J1.35, J2.18
D2: J1.33, J2.17
D3: J1.31, J2.16
D4: J1.29, J2.15
D5: J1.27, J2.14
D6: J1.25, J2.13
D7: J1.23, J2.12
EXP0: J1.6, J3.3
EXP1: J1.4, J3.2
EXP2: J1.21, J2.11
EXP3: J1.19, J2.10
GND: J1.1, J1.40, J2.1, J3.20
IRQB: J1.5, J2.3
NMIB: J1.7, J2.4
PHI2: J1.17, J2.9
RDY: J1.9, J2.5
RESB: J1.3, J2.2
RWB: J1.13, J2.7
SYNC: J1.15, J2.8
VCC: J1.2, J1.39, J2.20, J3.1

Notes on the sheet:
EXP0 and EXP1 carry HRDB (High ROM disable bar) in a build that uses cartridges: a cartridge grounds them to take $C000-$FFFF from the ROM. They are free only in a build that never uses cartridges. EXP2 and EXP3 are always free.

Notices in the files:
README.md:
License:
Hardware designs are released under the [CERN Open Hardware Licence Version 2 – Permissive](https://ohwr.org/cern_ohl_p_v2.txt).
Firmware is released under the MIT License — [KEH Controller](./Firmware/KEH%20Controller/LICENSE), [PS2 Keyboard Controller](./Firmware/PS2%20Keyboard%20Controller/LICENSE) and [SCP Controller](./Firmware/SCP%20Controller/LICENSE).
Hardware/Backplane/Rev 1.1/Backplane.kicad_pcb:
© 2024 A.C. Wright Design | acwrightdesign.com | Rev 1.1
Hardware/Memory Card/Rev 1.0/Memory Card.kicad_pcb:
© 2024 A.C. Wright Design | acwrightdesign.com | Rev 1.0
